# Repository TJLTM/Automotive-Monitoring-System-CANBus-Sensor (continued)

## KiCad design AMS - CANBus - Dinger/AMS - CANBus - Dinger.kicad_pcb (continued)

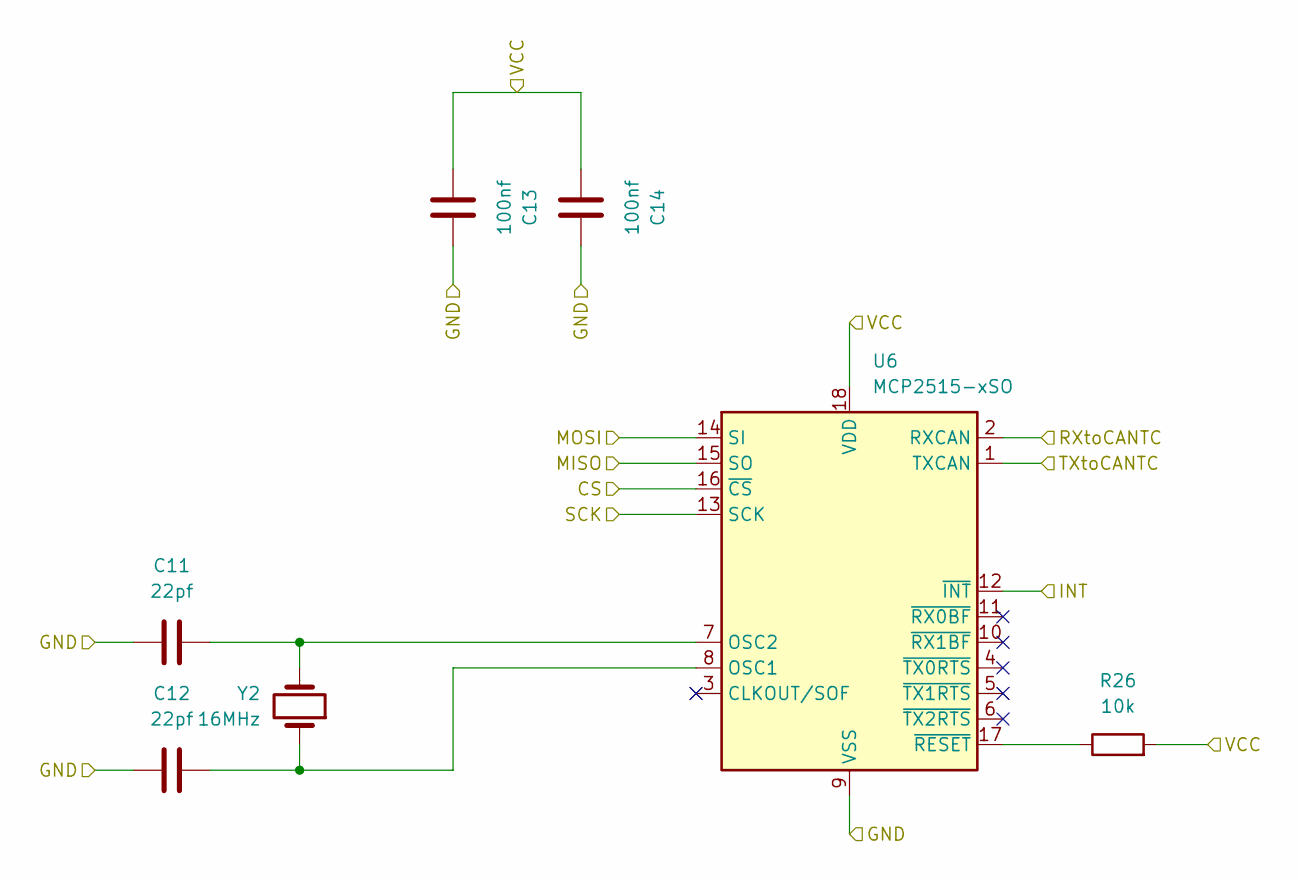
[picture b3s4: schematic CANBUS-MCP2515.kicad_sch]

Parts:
C11, C12: 22pf; C_1206_3216Metric_Pad1.33x1.80mm_HandSolder
C13, C14: 100nf; C_1206_3216Metric_Pad1.33x1.80mm_HandSolder
R26: 10k; R_1206_3216Metric_Pad1.30x1.75mm_HandSolder
U6: MCP2515-xSO; SOIC-18W_7.5x11.6mm_P1.27mm
Y2: 16MHz; Crystal_HC49-U_Vertical

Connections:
+5V: C13.1, C14.1, R26.2, U6.18 (VDD); also elsewhere on the board
/CANBUS-MCP2515/RXtoCANTC: U6.2 (RXCAN); also elsewhere on the board
/CANBUS-MCP2515/TXtoCANTC: U6.1 (TXCAN); also elsewhere on the board
D8: U6.12 (~INT); also elsewhere on the board
D10: U6.16 (~CS); also elsewhere on the board
GND: C11.2, C12.2, C13.2, C14.2, U6.9 (VSS); also elsewhere on the board
MISO: U6.15 (SO); also elsewhere on the board
MOSI: U6.14 (SI); also elsewhere on the board
unnamed: C12.1, U6.8 (OSC1), Y2.1
unnamed: C11.1, U6.7 (OSC2), Y2.2
unnamed: R26.1, U6.17 (~RESET)
SCK: U6.13 (SCK); also elsewhere on the board

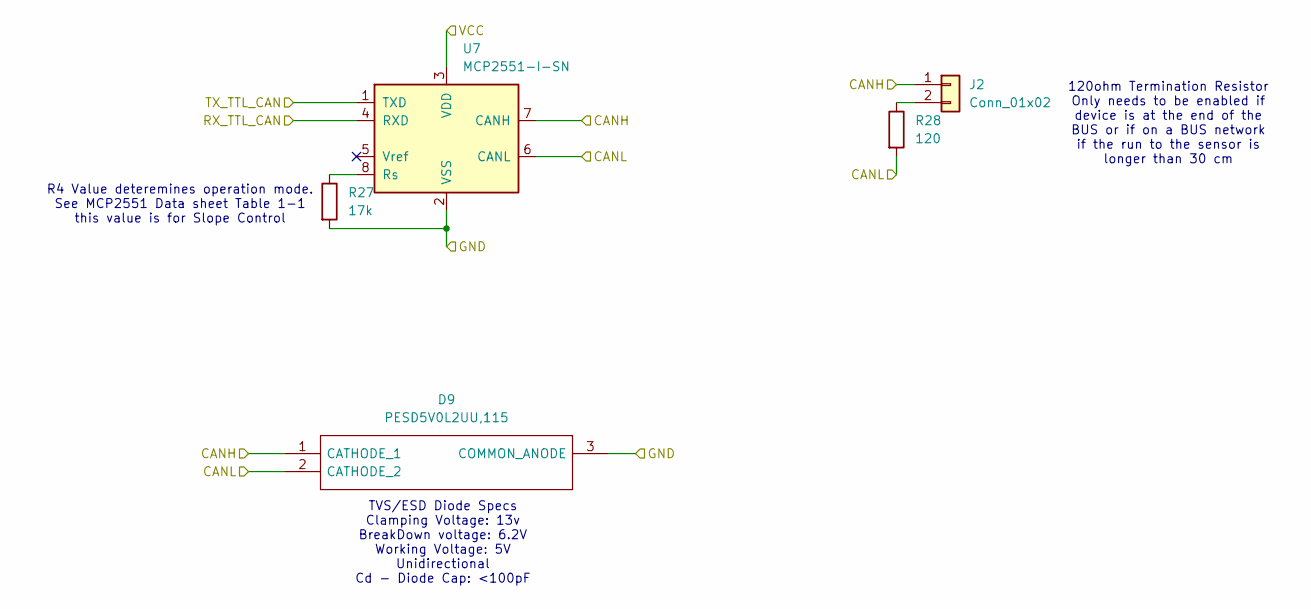
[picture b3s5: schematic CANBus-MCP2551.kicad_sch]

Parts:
D9: PESD5V0L2UU,115; SOT65P210X110-3N; Mouser Part Number 771-PESD5V0L2UU115
J2: Conn_01x02; PinHeader_1x02_P2.54mm_Vertical
R27: 17k; R_Axial_DIN0204_L3.6mm_D1.6mm_P1.90mm_Vertical
R28: 120; R_Axial_DIN0204_L3.6mm_D1.6mm_P1.90mm_Vertical
U7: MCP2551-I-SN; SOIC-8_3.9x4.9mm_P1.27mm

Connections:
+5V: U7.3 (VDD); also elsewhere on the board
/CANBUS-MCP2515/RXtoCANTC: U7.4 (RXD); also elsewhere on the board
/CANBUS-MCP2515/TXtoCANTC: U7.1 (TXD); also elsewhere on the board
CANBUS_H: D9.1 (CATHODE_1), J2.1, U7.7 (CANH); also elsewhere on the board
CANBUS_L: D9.2 (CATHODE_2), R28.2, U7.6 (CANL); also elsewhere on the board
GND: D9.3 (COMMON_ANODE), R27.2, U7.2 (VSS); also elsewhere on the board
unnamed: J2.2, R28.1
unnamed: R27.1, U7.8 (Rs)

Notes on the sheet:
TVS/ESD Diode Specs Clamping Voltage: 13v BreakDown voltage: 6.2V Working Voltage: 5V Unidirectional Cd - Diode Cap: <100pF
R4 Value deteremines operation mode. See MCP2551 Data sheet Table 1-1 this value is for Slope Control
120ohm Termination Resistor Only needs to be enabled if device is at the end of the BUS or if on a BUS network if the run to the sensor is longer than 30 cm

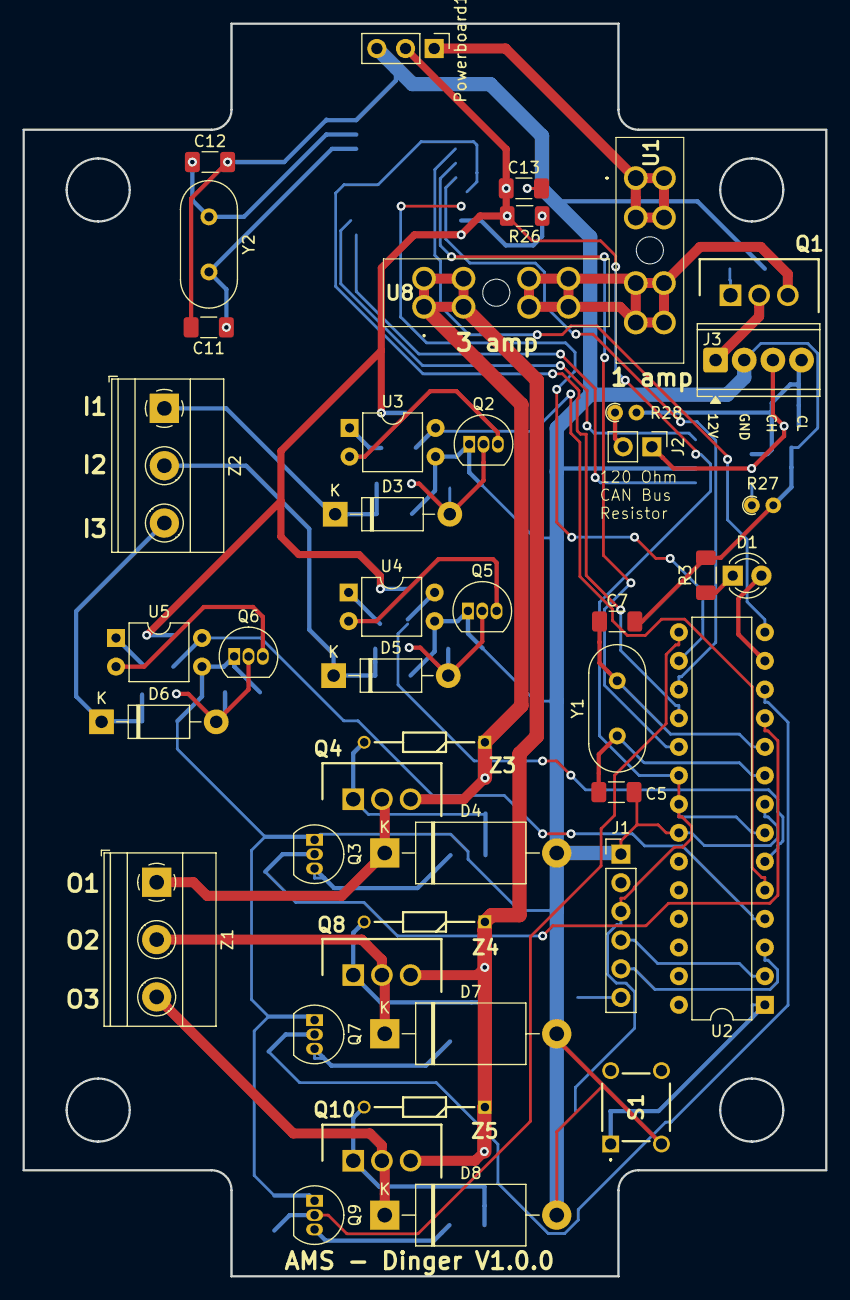
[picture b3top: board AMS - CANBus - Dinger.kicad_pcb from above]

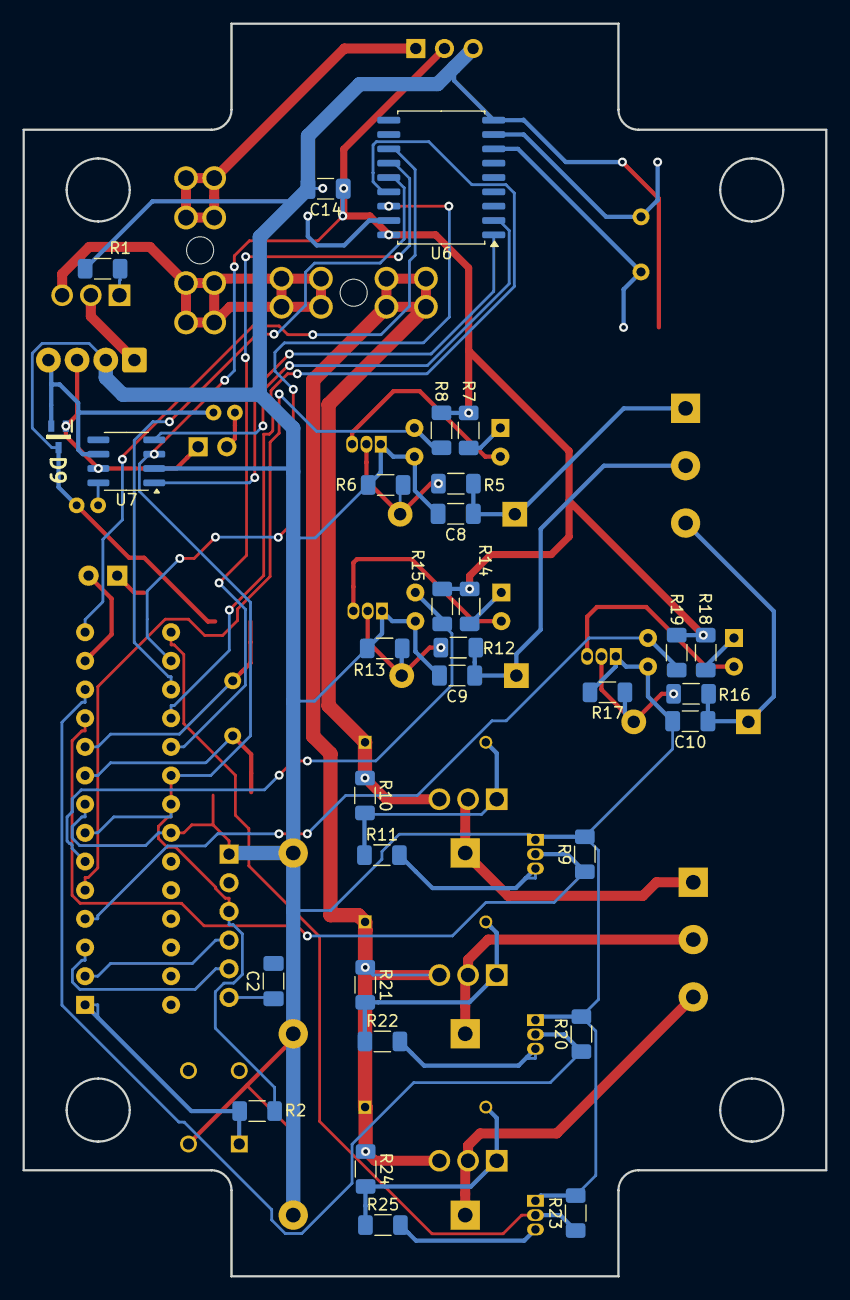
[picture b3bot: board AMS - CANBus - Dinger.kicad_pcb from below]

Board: 2 copper layers, 71.1 x 111.0 mm, 75 parts (31 on the bottom side), 56 nets.

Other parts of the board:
Q9: 2N7000; TO-92_Inline
R20: 1M; R_1206_3216Metric_Pad1.30x1.75mm_HandSolder

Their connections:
GND: Q9.1 (S), R20.2; also elsewhere on the board
unnamed 39: Q9.3 (D); also elsewhere on the board
Output2: R20.1; also elsewhere on the board
Output3: Q9.2 (G); also elsewhere on the board

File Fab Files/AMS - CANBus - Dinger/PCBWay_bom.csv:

Designator,Quantity,Value,Footprint,Package,MPN,DNP,Mount_Type,Description,Height,Mouser Part Number,Mouser Price/Stock,Manufacturer_Name
"C10, C8, C9",3,220nF,C_1206_3216Metric_Pad1.33x1.80mm_HandSolder,,,,smt,,,,,
"C11, C12",2,22pf,C_1206_3216Metric_Pad1.33x1.80mm_HandSolder,,,,smt,Unpolarized capacitor,,,,
"C13, C14, C2",3,100nf,C_1206_3216Metric_Pad1.33x1.80mm_HandSolder,,,,smt,Unpolarized capacitor,,,,
"C5, C7",2,22pF,C_1206_3216Metric_Pad1.33x1.80mm_HandSolder,,,,smt,,,,,
D1,1,LED,LED_D3.0mm,,,,tht,,,,,
"D3, D5, D6",3,1N4007,D_DO-41_SOD81_P10.16mm_Horizontal,,,,tht,,,,,
"D4, D7, D8",3,STPS3150RL,D_DO-201_P15.24mm_Horizontal,,,,tht,,,,,
D9,1,"PESD5V0L2UU,115",SOT65P210X110-3N,,"PESD5V0L2UU,115",,smt,"Nexperia PESD5V0L2UU,115, Dual-Element Uni-Directional ESD Protection Diode, 70W, 3-Pin SOT-323",1.1,771-PESD5V0L2UU115,https://www.mouser.co.uk/ProductDetail/Nexperia/PESD5V0L2UU1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,Nexperia
J1,1,TTL_Programmer,PinHeader_1x06_P2.54mm_Vertical,,,,tht,"Generic connector, single row, 01x06, script generated (kicad-library-utils/schlib/autogen/connector/)",,,,
J2,1,Conn_01x02,PinHeader_1x02_P2.54mm_Vertical,,,,tht,"Generic connector, single row, 01x02, script generated (kicad-library-utils/schlib/autogen/connector/)",,,,
J3,1,Power_And_CAN,"TerminalBlock_Phoenix_MPT-0,5-4-2.54_1x04_P2.54mm_Horizontal",,,,tht,"Generic screw terminal, single row, 01x04, script generated (kicad-library-utils/schlib/autogen/connector/)",,,,
Powerboard1,1,Conn_01x03,PinHeader_1x03_P2.54mm_Vertical,,,,tht,"Generic connector, single row, 01x03, script generated (kicad-library-utils/schlib/autogen/connector/)",,,,
"Q1, Q10, Q4, Q8",4,IRF9Z34NPBF,TO254P469X1042X1967-3P,,IRF9Z34NPBF,,tht,MOSFET MOSFT PCh -55V -17A 100mOhm 23.3nC,4.69,942-IRF9Z34NPBF,https://www.mouser.co.uk/ProductDetail/Infineon-IR/IRF9Z34NP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,Infineon
"Q2, Q3, Q5, Q6, Q7, Q9",6,2N7000,TO-92_Inline,,,,tht,,,,,
"R1, R11, R22, R25, R26",5,10k,R_1206_3216Metric_Pad1.30x1.75mm_HandSolder,,,,smt,Resistor,,,,
"R10, R21, R24",3,100k,R_1206_3216Metric_Pad1.30x1.75mm_HandSolder,,,,smt,,,,,
"R12, R16, R5",3,470,R_1206_3216Metric_Pad1.30x1.75mm_HandSolder,,,,smt,,,,,
"R13, R14, R15, R17, R18, R19, R6, R7, R8",9,5k,R_1206_3216Metric_Pad1.30x1.75mm_HandSolder,,,,smt,,,,,
"R2, R3",2,330,R_1206_3216Metric_Pad1.30x1.75mm_HandSolder,,,,smt,,,,,
"R20, R23, R9",3,1M,R_1206_3216Metric_Pad1.30x1.75mm_HandSolder,,,,smt,,,,,
R27,1,17k,R_Axial_DIN0204_L3.6mm_D1.6mm_P1.90mm_Vertical,,,,tht,Resistor,,,,
R28,1,120,R_Axial_DIN0204_L3.6mm_D1.6mm_P1.90mm_Vertical,,,,tht,Resistor,,,,
S1,1,TS02-66-160-BK-260-LCR-D,TS0266160BK260LCRD,,TS02-66-160-BK-260-LCR-D,,tht,"Tactile Switches 6 x 6 mm, 16 mm Act Height, 260 gf, Black, Long Crimped, Through Hole, SPST,",16.2,179-TS0266160BK260LC,https://www.mouser.co.uk/ProductDetail/CUI-Devices/TS02-66-1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,CUI Devices
"U1, U8",2,178.6165.0001,17861650001,,178.6165.0001,,tht,FLR PCB FUSE HOLDER FOR ATO STYLE BLADE FUSE RATED 58V,17.5,576-178.6165.0001,https://www.mouser.co.uk/ProductDetail/Littelfuse/1786165000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,LITTELFUSE
U2,1,ATmega328-P,DIP-28_W7.62mm,,,,tht,,,,,
"U3, U4, U5",3,LTV-817,DIP-4_W7.62mm,,,,tht,,,,,
U6,1,MCP2515-xSO,SOIC-18W_7.5x11.6mm_P1.27mm,,,,smt,"Stand-Alone CAN Controller with SPI Interface, SOIC-18",,,,
U7,1,MCP2551-I-SN,SOIC-8_3.9x4.9mm_P1.27mm,,,,smt,"High-Speed CAN Transceiver, 1Mbps, 5V supply, SOIC-8",,,,
Y1,1,Crystal,Crystal_HC49-U_Vertical,,,,tht,,,,,
Y2,1,16MHz,Crystal_HC49-U_Vertical,,,,tht,Two pin crystal,,,,
"Z1, Z2",2,Screw_Terminal_01x03,"TerminalBlock_Phoenix_MKDS-1,5-3-5.08_1x03_P5.08mm_Horizontal",,,,tht,,,,,
"Z3, Z4, Z5",3,BZX79C10,DIOAD1068W53L380D172,,BZX79C10,,tht,"BZX79C10, Zener Diode, 10V +/-5 500 mW 0.2A, 2-Pin DO-35",,512-BZX79C10,https://www.mouser.co.uk/ProductDetail/ON-Semiconductor-Fair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,ON Semiconductor

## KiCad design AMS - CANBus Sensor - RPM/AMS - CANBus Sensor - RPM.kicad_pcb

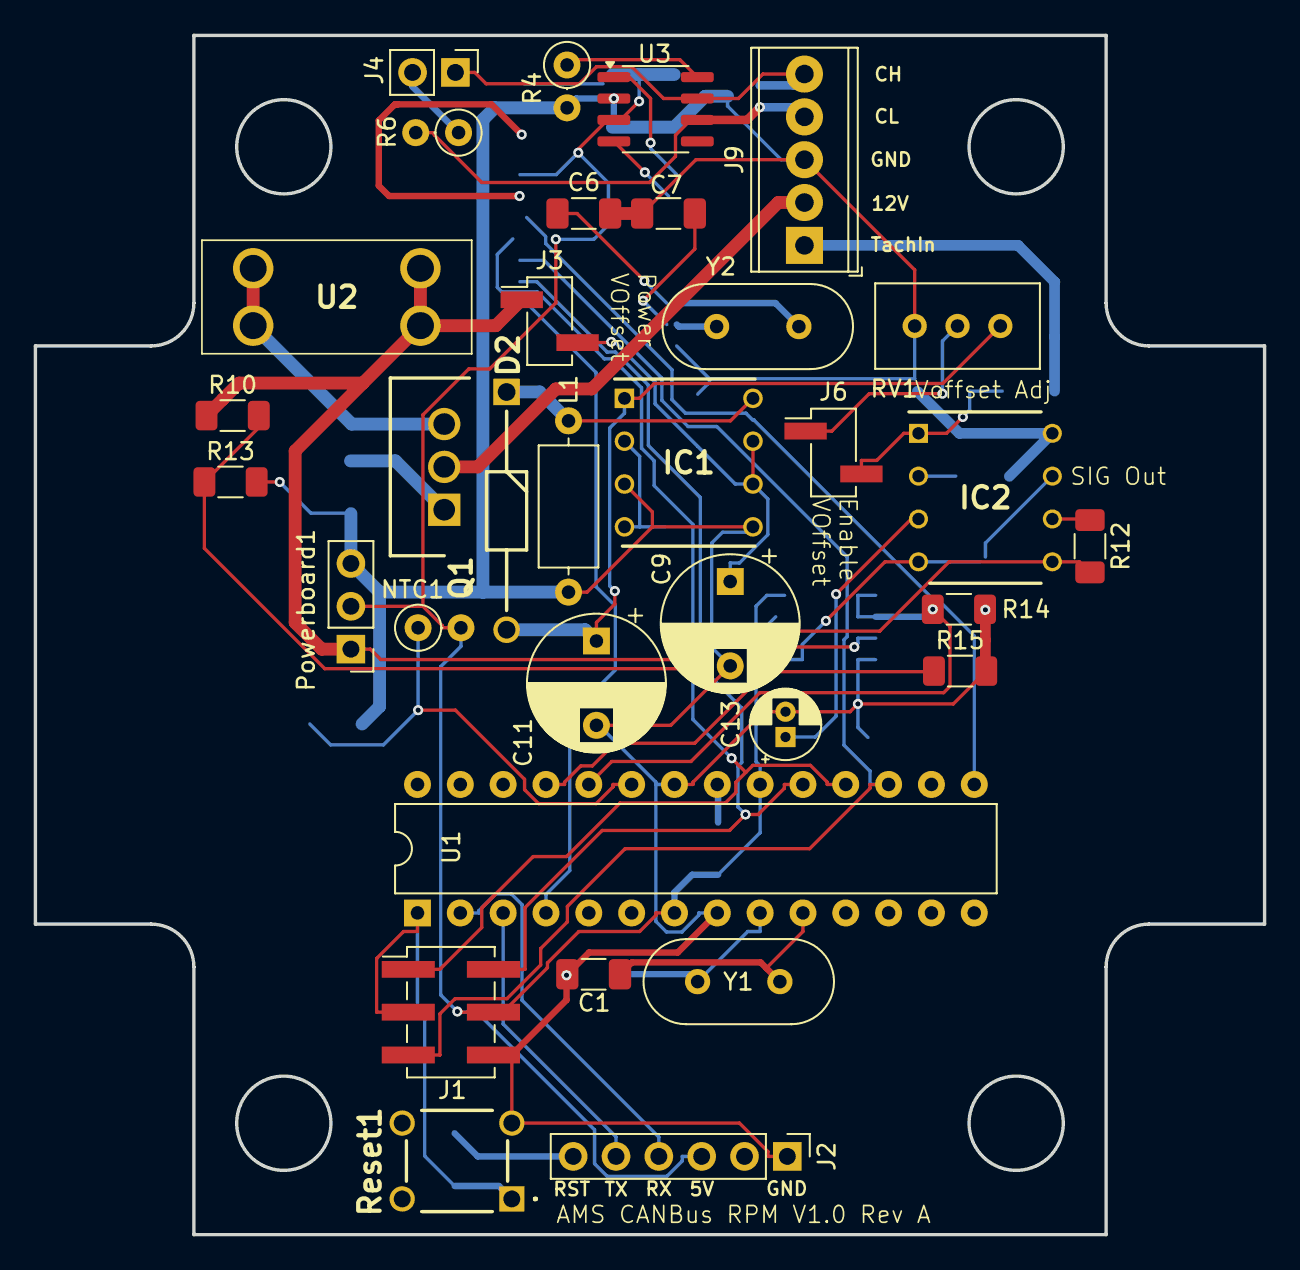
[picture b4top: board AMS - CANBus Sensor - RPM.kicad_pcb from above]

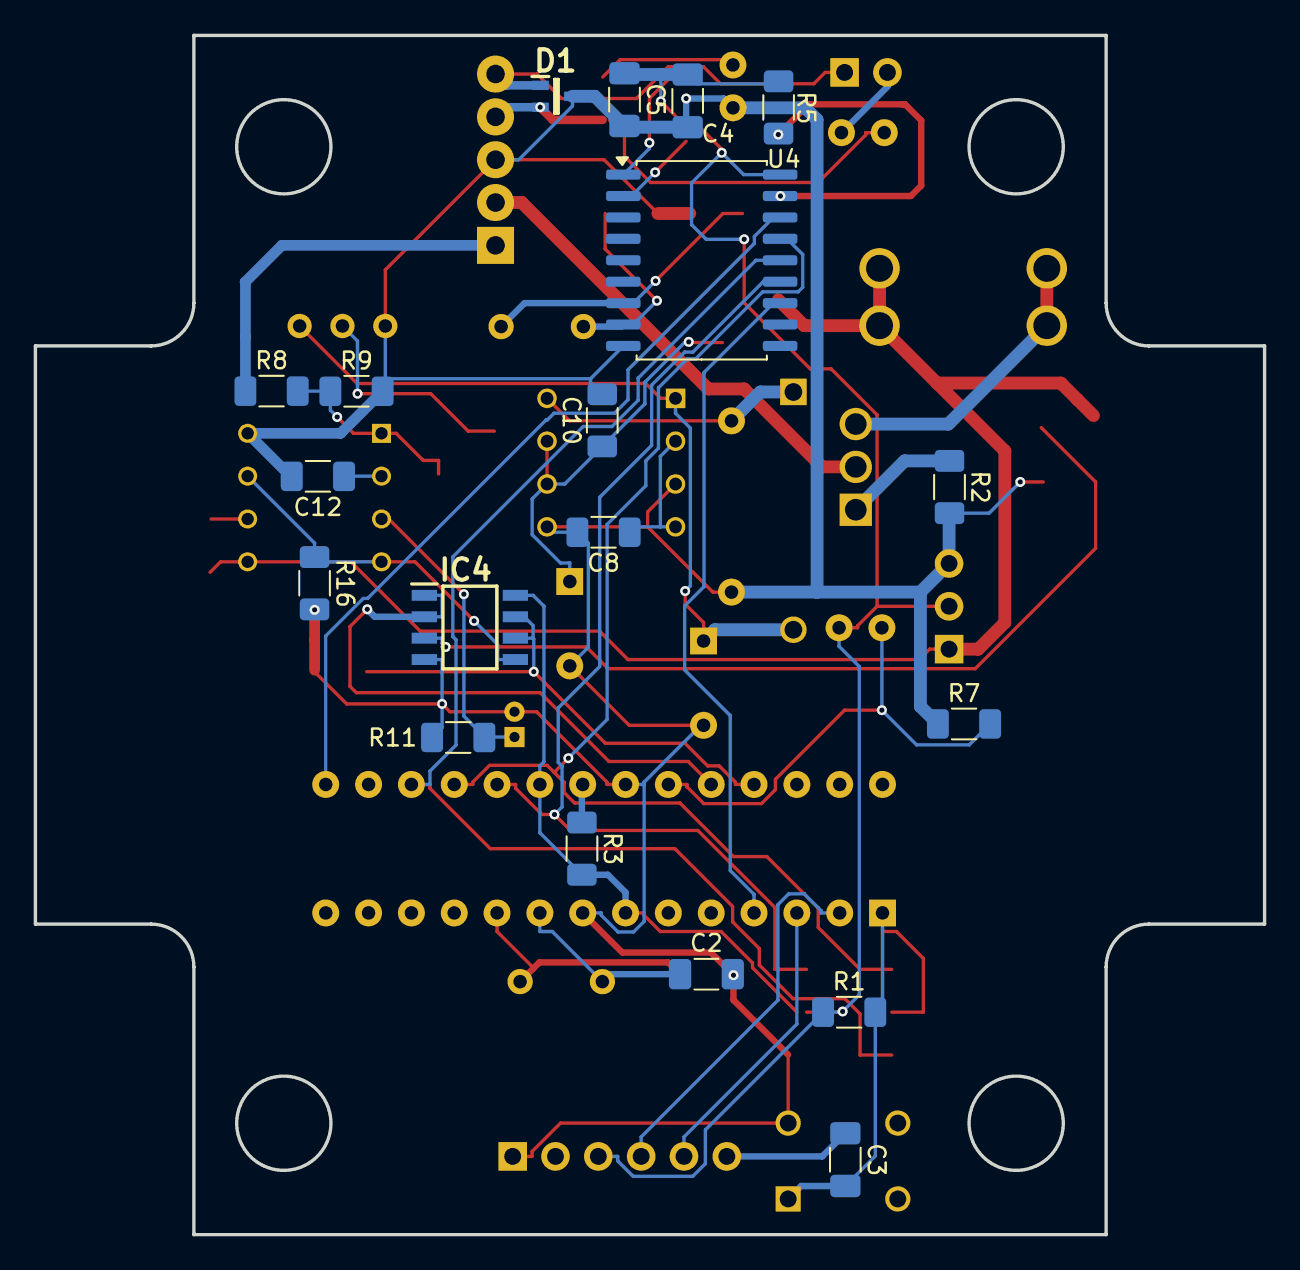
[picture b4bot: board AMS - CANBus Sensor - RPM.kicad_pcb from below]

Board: 2 copper layers, 72.9 x 71.1 mm, 52 parts (19 on the bottom side), 42 nets.

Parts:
C1, C2, C6, C7: 22pf; C_1206_3216Metric_Pad1.33x1.80mm_HandSolder
C3, C4, C5: 100nf; C_1206_3216Metric_Pad1.33x1.80mm_HandSolder
C8, C10: 0.1uF; R_1206_3216Metric_Pad1.30x1.75mm_HandSolder
C9: 120uF; CP_Radial_D8.0mm_P5.00mm
C11: 68uF; CP_Radial_D8.0mm_P5.00mm
C12: 0.02uF; R_1206_3216Metric_Pad1.30x1.75mm_HandSolder
C13: 1uF; CP_Radial_D4.0mm_P1.50mm
D1: PESD5V0L2UU,115; SOT65P210X110-3N
D2: 1N5817; DIOAD1414W86L464D238
IC1: MAX764CPA+; DIP762W56P254L938H457Q8N
IC2: LM2917N-8_NOPB; DIP794W53P254L959H508Q8N
IC4: OPA2340UA_2K5; SOIC127P600X175-8N
J1: ICSP; PinHeader_2x03_P2.54mm_Vertical_SMD
J2: TTL_Programmer; PinHeader_1x06_P2.54mm_Vertical
J3, J6: Conn_01x02; PinHeader_1x02_P2.54mm_Vertical_SMD_Pin1Left
J4: Conn_01x02; PinHeader_1x02_P2.54mm_Vertical
J9: Screw_Terminal_01x05; TerminalBlock_Phoenix_MPT-0,5-5-2.54_1x05_P2.54mm_Horizontal
L1: 47uH; L_Axial_L7.0mm_D3.3mm_P10.16mm_Horizontal_Fastron_MICC
NTC1: 10k; R_Axial_DIN0207_L6.3mm_D2.5mm_P2.54mm_Vertical
Powerboard1: Conn_01x03; PinHeader_1x03_P2.54mm_Vertical
Q1: IRF9Z34NPBF; TO254P469X1042X1967-3P
R1, R2, R5, R7, R8: 10k; R_1206_3216Metric_Pad1.30x1.75mm_HandSolder
R3: 4.7k; R_1206_3216Metric_Pad1.30x1.75mm_HandSolder
R4: 17k; R_Axial_DIN0207_L6.3mm_D2.5mm_P2.54mm_Vertical
R6: 120; R_Axial_DIN0207_L6.3mm_D2.5mm_P2.54mm_Vertical
R9: 22k; R_1206_3216Metric_Pad1.30x1.75mm_HandSolder
R10: 120k; R_1206_3216Metric_Pad1.30x1.75mm_HandSolder
R11, R16: 100k; R_1206_3216Metric_Pad1.30x1.75mm_HandSolder
R12: 470; R_1206_3216Metric_Pad1.30x1.75mm_HandSolder
R13: 15k; R_1206_3216Metric_Pad1.30x1.75mm_HandSolder
R14, R15: 47k; R_1206_3216Metric_Pad1.30x1.75mm_HandSolder
RV1: 100k; Potentiometer_Bourns_3296W_Vertical
Reset1: TS02-66-160-BK-260-LCR-D; TS0266160BK260LCRD
U1: ATmega328P-P; DIP-28_W7.62mm
U2: 3568
U3: MCP2551-I-SN; SOIC-8_3.9x4.9mm_P1.27mm
U4: MCP2515-xSO; SOIC-18W_7.5x11.6mm_P1.27mm
Y1, Y2: 16MHz; Crystal_HC49-U_Vertical

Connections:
+5V: C4.1, C5.1, IC4.8 (V+), J1.4, J2.3, NTC1.2, Powerboard1.2, R1.1, R3.2, R5.2, U1.7 (VCC), U1.20 (AVCC), U3.3 (VDD), U4.18 (VDD)
+VDC: IC2.5 (COL), J3.1, Powerboard1.1, R10.1, R12.2, U2.3, U2.4
/BareMinAtmel328P/AREF: R3.1, U1.21 (AREF)
/BareMinAtmel328P/PB1-D9: U1.15 (PB1), U4.16 (~CS)
/BareMinAtmel328P/PB3-D11-MOSI: J1.5, U1.17 (PB3), U4.14 (SI)
/BareMinAtmel328P/PB4-D12-MISO: J1.1, U1.18 (PB4), U4.15 (SO)
/BareMinAtmel328P/PB5-D13-SCK: J1.2, U1.19 (PB5), U4.13 (SCK)
/BareMinAtmel328P/PC0-A0: NTC1.1, R7.2, U1.23 (PC0)
/BareMinAtmel328P/PC1-A1: IC4.1 (OUT_A), IC4.2 (-INA), R14.1, U1.24 (PC1)
/BareMinAtmel328P/PC2-A2: IC4.6 (-IN_B), IC4.7 (OUTB), R15.1, U1.25 (PC2)
/BareMinAtmel328P/PD0-RX: J2.4, U1.2 (PD0)
/BareMinAtmel328P/PD1-TX: J2.5, U1.3 (PD1)
/BareMinAtmel328P/PD2-D2: U1.4 (PD2), U4.12 (~INT)
/BareMinAtmel328P/RESET: C3.2, J1.3, R1.2, Reset1.1 (NO_1), U1.1 (~RESET/PC6)
/CANBUS-MCP2515/RXtoCANTC: U3.4 (RXD), U4.2 (RXCAN)
/CANBUS-MCP2515/TXtoCANTC: U3.1 (TXD), U4.1 (TXCAN)
/RPM_Sensor/RPM-Vout: IC2.4 (EMIT), IC2.7 (IN-), IC4.5 (+INB), R16.1
CANBUS_H: D1.1 (CATHODE_1), J4.1, J9.5, U3.7 (CANH)
CANBUS_L: D1.2 (CATHODE_2), J9.4, R6.2, U3.6 (CANL)
GND: C1.2, C2.2, C4.2, C5.2, C6.2, C7.2, C8.2, C9.2, C10.2, C11.2, C12.2, C13.2, D1.3 (COMMON_ANODE), IC1.3 (SHDN), IC1.5 (GND), IC2.8 (TACH-/GND), IC4.4 (V-), J1.6, J2.1, J9.3, L1.2, Powerboard1.3, R2.2, R4.2, R7.1, R9.2, R11.2, R13.2, R14.2, R15.2, R16.2, RV1.3, Reset1.3 (COM_1), U1.8 (GND), U1.22 (GND), U3.2 (VSS), U4.9 (VSS)
unnamed: C8.1, IC1.2 (FB), IC1.4 (REF)
unnamed: D2.1, IC1.8 (LX), L1.1
unnamed: C11.1, D2.2, IC1.1 (OUT), RV1.1
unnamed: C9.1, C10.1, IC1.6 (V+_1), IC1.7 (V+_2), J3.2
unnamed: C12.1, IC2.2 (CP1)
unnamed: C13.1, IC2.3 (CP2/IN+), R11.1
unnamed: IC2.1 (TACH+), J6.2, R8.2, R9.1
unnamed: IC2.6 (V+), R12.1
unnamed: IC4.3 (+IN_A), R10.2, R13.1
unnamed: C3.1, J2.6
unnamed: J4.2, R6.1
unnamed: J6.1, RV1.2
unnamed: J9.2, Q1.2
unnamed: Q1.1, R2.1
unnamed: Q1.3, U2.1, U2.2
unnamed: C2.1, U1.9 (XTAL1/PB6), Y1.2
unnamed: C1.1, U1.10 (XTAL2/PB7), Y1.1
unnamed: R4.1, U3.8 (Rs)
unnamed: C7.1, U4.8 (OSC1), Y2.1
unnamed: C6.1, U4.7 (OSC2), Y2.2
unnamed: R5.1, U4.17 (~RESET)
TachIn: J9.1, R8.1

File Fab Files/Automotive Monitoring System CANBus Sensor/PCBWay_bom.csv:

designator,quantity,value,pack,mpn,mount_type
"C1, C2, C6, C7",4,22pf,C_1206_3216Metric_Pad1.33x1.80mm_HandSolder,,smt
"C3, C4, C5",3,100nf,C_1206_3216Metric_Pad1.33x1.80mm_HandSolder,,smt
D1,1,"PESD5V0L2UU,115",SOT65P210X110-3N,,smt
J1,1,ICSP,PinHeader_2x03_P2.54mm_Vertical_SMD,,smt
J2,1,TTL_Programmer,PinHeader_1x06_P2.54mm_Vertical,,tht
J4,1,Conn_01x02,PinHeader_1x02_P2.54mm_Vertical,,tht
J5,1,Power_And_CAN,"TerminalBlock_Phoenix_MPT-0,5-4-2.54_1x04_P2.54mm_Horizontal",,tht
J6,1,Conn_02x08_Odd_Even,PinHeader_2x08_P2.54mm_Vertical,,tht
NTC1,1,10k,R_Axial_DIN0207_L6.3mm_D2.5mm_P2.54mm_Vertical,,tht
Powerboard1,1,Conn_01x03,PinHeader_1x03_P2.54mm_Vertical,,tht
Q1,1,IRF9Z34NPBF,TO254P469X1042X1967-3P,,tht
"R1, R2, R5, R7",4,10k,R_1206_3216Metric_Pad1.30x1.75mm_HandSolder,,smt
R3,1,4.7k,R_1206_3216Metric_Pad1.30x1.75mm_HandSolder,,smt
R4,1,17k,R_Axial_DIN0207_L6.3mm_D2.5mm_P2.54mm_Vertical,,tht
R6,1,120,R_Axial_DIN0207_L6.3mm_D2.5mm_P2.54mm_Vertical,,tht
Reset1,1,TS02-66-160-BK-260-LCR-D,TS0266160BK260LCRD,,tht
U1,1,ATmega328P-P,DIP-28_W7.62mm,,tht
U2,1,178.6165.0001,17861650001,,tht
U3,1,MCP2551-I-SN,SOIC-8_3.9x4.9mm_P1.27mm,,smt
U4,1,MCP2515-xSO,SOIC-18W_7.5x11.6mm_P1.27mm,,smt
"Y1, Y2",2,16MHz,Crystal_HC49-U_Vertical,,tht

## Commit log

2024-04-06 initial KICAD 8 project
2024-04-06 initial with the 328p base sheet.
2024-04-06 removing the lock file. added by accident.
2024-04-08 have the basic schems in need to assign footprints and do the PCB layout.
2024-04-09 ok updated the footprints. now toi get the DRC and a then PCB layout
2024-04-09 ERC passed added footprints to PCB
2024-04-10 tweaked footprints and made a bunch SMD for space saving. getting the board mostly placed before routing.
2024-04-11 Prerouting
2024-04-12 placed and power gnd routed
2024-04-12 autorouted the rest
2024-04-12 DRC check and fixes
2024-04-12 adding Fab Files
2024-05-12 updated the 22nF to 22pF for the 16 MHz crystals so they would be correct values.
2024-05-12 ammending my last commit to have the correct cap values of 22pF
2024-05-12 adding the second base design based on teh SMD automotive temp version of the 328P
2024-05-19 working on the SMD version Making The Pressure version based off of the DIP Package
2024-05-20 wip for this trying to figure out if i want to go completely SMD with this or not.
2024-05-24 ready for fab
2024-05-24 adding this for the RPM sensor
2024-05-24 wip for RPM
2024-05-24 cloning the Pressure board since this is the size i'm going to have to go with and most of the work is done.
2024-05-25 wip for the temp sensor
2024-05-25 cloning pressure for Vacuum sensor
2024-05-25 wip for the vacuum
2024-05-25 adding the vac sensor subsheet
2024-05-25 Temp Sensor Done
2024-05-25 adding fab files for Pressure and Temp sensors
2024-05-25 i think the Vacuum sensor is done i need to test s afew things and then this is ready for fab
2024-05-25 vacuum wip
2024-05-26 Create LICENSE
2024-05-27 adding IO wip
2024-06-02 Temperature Sensor board 1.0 REV. B
    flipped the 3.3v and op amp to the back of the board to make assembly on a hotplate easier for the harder to place and solder components.
2024-06-08 removing the 2.5v ref and putting in -5v rail. need to prototype this out to viability
2024-06-08 Pressure Sensor 1.0 Rev B boards. My dyslexic asss flipped the power pin out from the boards i have designed
2024-06-08 Temperature Board v1.0 Rev C.
    fixing my other dyslexic fuck up for the power on this board as well
2024-06-08 fixing the same powerboard problem on the remaining boards.
2024-06-14 flipped the powerboard input to match the designs i have.
2024-06-16 clean up and start of the work for the PCB
2024-06-16 Initial RGB Board
2024-06-16 removal of the Input stuff from the Voltage Board this was copied from
2024-06-16 removing this as it's not needed.
2024-06-16 Removing The General RGB project and split them into NChannel (12V out) and PChannel (Ground) as to pick a board on the hardware you have.
2024-06-17 RGB - Nchannel done and routed. V1.0 Rev A
2024-06-17 RGB - PChannel V1.0 Rev A Done and routed.
2024-06-17 forgot to add this in as it's needed for you know it to work...
2024-06-17 RGB N and P Channel Boards Release.
2024-06-21 adding in DXF for the other two holes i didn't account for in placing parts on the board
2024-06-21 adding the holes i deleted so i make sure i don't place parts on the bottom of the board when doing things.
2024-06-21 fixed the problems with having stuff overlapping the bosses in the serpac enclosures.
2024-06-21 clean up to avoid serpac case mounting bosses.
2024-06-23 updated fab files for RGB Boards
2024-06-23 updating fab files for Pressure and Temperature boards
2024-06-23 RPM Sensor is done.
2024-06-23 RPM Sensor Fab Files
2024-07-24 removed un-needed BufferedADC.kicad_sch from IO and Temp boards as that was copied over.
    R8,9,14,15 100k resistors were removed from the ADC input and in parallel witht he 200k pots and then moved to be in series with the pots and changed to 1k
2024-07-28 adding fab files for Pressure Sensor
2024-08-05 initial name changes
2024-08-05 Another rename
2024-08-05 rename of the fab files
2024-08-05 update of fab files, regenerated
2024-08-22 update for my screw up for the power to the RTD chips
2024-08-22 renaming this to make it clear that these are RTD based Temp sensors
2024-08-22 rename for temp sensor
2024-08-22 updating FAB files for RTD temp sensor
2024-11-22 RTD Sensor V1.1 Rev B
    swapped 0.1 MM pitch header pins for 0.1In pitch
2024-11-22 Vacuum clean up of edge cuts.
2024-11-22 vacuum pcb moved components to clear mount bosses in case
2024-11-22 Vacuum Sensor V1.0.
2024-11-23 swaping to a dual rail setup.
2024-11-23 picking upt whatever i missed.
2025-01-28 adding the Mounting Plate for the Current Sensor and STL
2025-03-02 Adding Dinger thing
2025-03-14 initial placement of parts
2025-03-14 pre freerouting
2025-03-14 Dinger V1.0.0 Files done and submitted for FAB
2025-03-14 adding the special spacer that if you put two boards into a single RB5 serpac
2025-03-19 adding a tool that is helpful when i have to make these
2025-04-01 adding the one for the dinger
2025-08-07 routing and stuff are fixed along with the addition of the I2c bus being pulled out.
2025-08-07 initial change. the local NTC temp sensor will have to be removed due to limitations with ADC pins
2025-08-14 wip for this.
2025-08-14 initial change from a bad low side switch to a high side switch
2025-11-01 logger wip
2025-11-01 i think this is ready
2025-11-02 finished the regular format adding the uno shield
2025-11-02 logger shield routed
2025-11-23 Logger Shield fixing the following Fuck ups for 1.0 Rev A * didn't connect the 3.3v lines * didn't connect the 5.5v SD Card Chip Select to the level shifter * didn't connect the VDC to the Vin pin
    Did some route optimization with my widdle brain.
    Bumped to Rev B since i didn't fix any that was not a complete fuck up or add anything new
2025-12-02 removing the fab files cause at this point if someone is going to make something they are going to use the appropriate tools for their PCB fab service
